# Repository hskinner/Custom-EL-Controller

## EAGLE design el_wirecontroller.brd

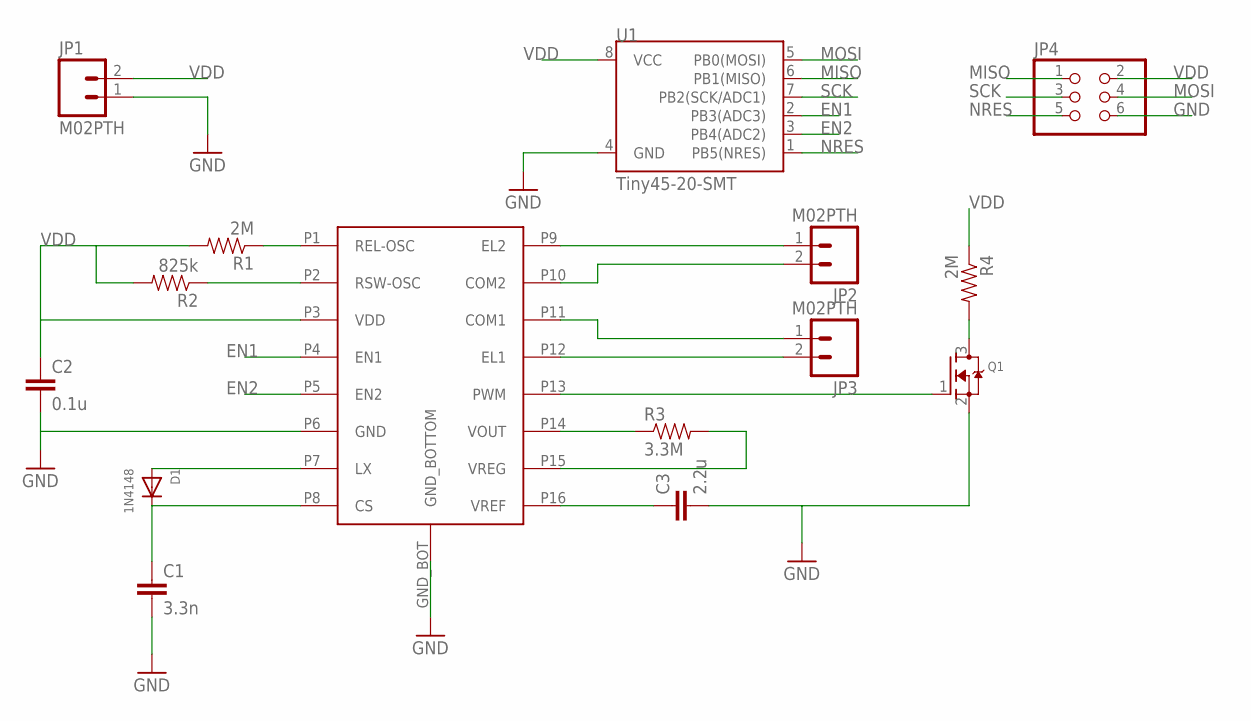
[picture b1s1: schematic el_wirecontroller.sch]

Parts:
C1: 3.3n; 0402-CAP
C2: 0.1u; 0402-CAP
C3: 2.2u; 0402-CAP
D1: 1N4148; DO-1N4148
JP1, JP2, JP3: M02PTH; 1X02
JP4: PINHD-2X3; 2X03
Q1: MOSFET-NREFLOW; SOT23
R1, R4: 2M; 0402-RES
R2: 825k; 0402-RES
R3: 3.3M; 0402-RES
U1: Tiny45-20-SMT; SO08-EIAJ
U$1: HV861; QFN-16

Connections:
EN1: U1.2 (PB3(ADC3)), U$1.P4 (EN1)
EN2: U1.3 (PB4(ADC2)), U$1.P5 (EN2)
GND: C1.2, C2.2, C3.2, JP1.1, JP4.6, Q1.2 (S), U1.4 (GND), U$1.GND_BOT (GND_BOTTOM), U$1.P6 (GND)
MISO: JP4.1, U1.6 (PB1(MISO))
MOSI: JP4.4, U1.5 (PB0(MOSI))
unnamed: R1.1, U$1.P1 (REL-OSC)
unnamed: R2.1, U$1.P2 (RSW-OSC)
unnamed: Q1.1 (G), U$1.P13 (PWM)
unnamed: C3.1, U$1.P16 (VREF)
unnamed: D1.A, U$1.P7 (LX)
unnamed: C1.1, D1.C, U$1.P8 (CS)
unnamed: JP2.1, U$1.P9 (EL2)
unnamed: R3.1, U$1.P14 (VOUT)
unnamed: R3.2, U$1.P15 (VREG)
unnamed: JP2.2, U$1.P10 (COM2)
unnamed: JP3.1, U$1.P11 (COM1)
unnamed: JP3.2, U$1.P12 (EL1)
unnamed: Q1.3 (D), R4.2
NRES: JP4.5, U1.1 (PB5(NRES))
SCK: JP4.3, U1.7 (PB2(SCK/ADC1))
VDD: C2.1, JP1.2, JP4.2, R1.2, R2.2, R4.1, U1.8 (VCC), U$1.P3 (VDD)

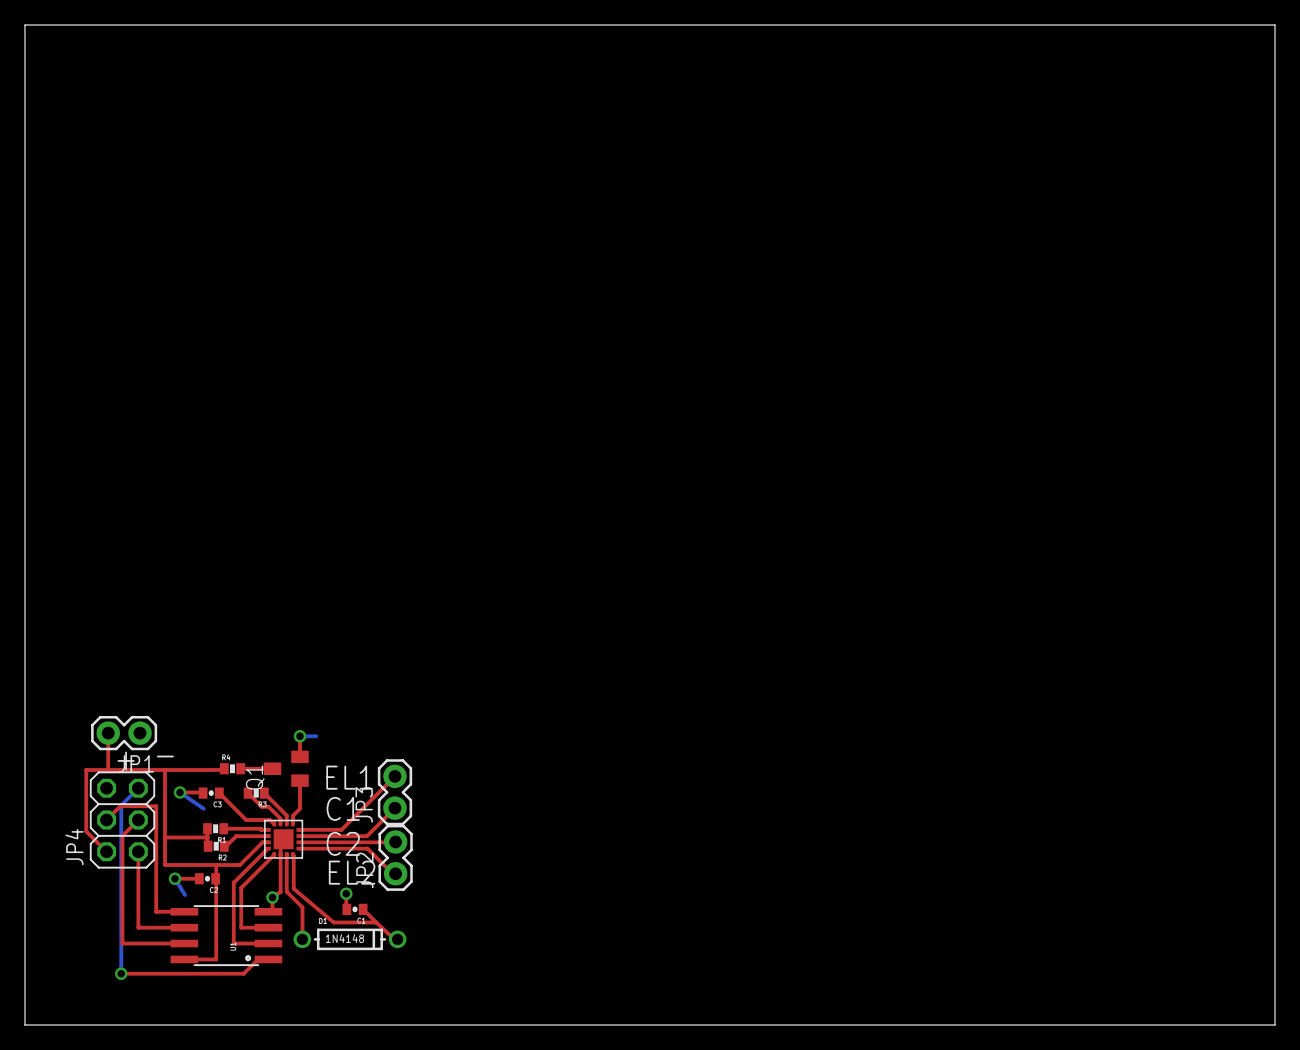
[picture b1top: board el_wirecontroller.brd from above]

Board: 2 copper layers, 100.0 x 80.0 mm, 15 parts (0 on the bottom side), 21 nets.

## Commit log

2015-06-24 initial version of EL controller board
2015-06-24 add transistor

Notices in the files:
parts and their libraries:
SparkFun-Passives: Licensing: CC v3.0 Share-Alike You are welcome to use this library for commercial purposes.
